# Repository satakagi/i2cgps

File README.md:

# I2CGPS

これは一般的なGPSレシーバ (GY-NEO6MV2など、UART 9600bpsでNMEA0183形式のデータを出力する。3.3Vでも動くもの) をI2Cインターフェースで使用できるようにするものです。メインコンピューターのUARTに余裕がないときに便利かもしれません。Arduino Pro Mini 3.3V (8MHz)でI2Cに変換しています。GY-NEO6MV2+Arduino Pro Mini 3.3V互換ボード+CHIRIMEN PiZero環境で動作確認をしました。

https://github.com/ckuethe/i2cgps をフォークして開発しました。そのため、i2cのインターフェース仕様はフォーク元に準じます。
ただ、私のArduino環境ではオリジナルのソース(.ino)はうまく動かなかったので、GPSライブラリの変更を伴う作り直しをしています。

原作者さんはATTiny85への移行を目指したようですが未達、この実装もArduino(ATMega248)用です。

また、以下を追加しています。
* [chirimen](https://www.chirimen.org)用のドライバとサンプル：[chirimen](./chirimen/)ディレクトリ
* 実体配線図：[hardware](./hardware)
* 未検証ですが・・KiCadのプリント基板設計図：[hardware/KiCad/](./hardware/KiCad/)

## 準備するもの
* GPSレシーバ([GY-NEO6MV2](https://electronicwork.shop/items/625c1ca99fe3d707d725cbe1)で確認しています)
* Arduiono Pro Mini 3.3V (8MHz) （もしくはその互換ボード）：この配線図通りで動かすには3.3V版が必要です ([互換ボードは数百円](https://electronicwork.shop/items/64e2182be37f74003b45e342)で購入できると思います)
* Arduiono Pro Miniにファームウェア(スケッチ)を書き込むための環境(ハードとしてはFTDI USBシリアル変換アダプター([数百円](https://electronicwork.shop/items/63412a95c15c5a192180482f)で買えると思います)が必要です)
* [Chirimen Pi Zero 環境](https://tutorial.chirimen.org/pizero/)

## 動かし方
* ファームウェアの書き込み：Arduino Pro Mini 3.3V(もしくはその互換ボード)にUSB-シリアル(専用のものが安価に流通しています)に、ArduinoIDEで[i2cgps.ino](./i2cgps.ino)を書き込みます
* 実体配線図のようにつなぎます
* GPSレシーバが測位できていなくても、空のデータが送信されてくるため、Arduino側のLEDは点滅するはずです（点滅していないときはどこかに問題がある）
* 測位できるとGPSレシーバ側のLEDも点滅します(GY-NEO6MV2の場合)
* chirimen piZero環境で[サンプルコード(ドライバ付き)](./chirimen/main.js)を実行すると、データが出力されます

## 実体配線図

## ライセンス
ライセンスは原作者さんが明示していないので・・・　[The TAPR Open Hardware License](https://tapr.org/the-tapr-open-hardware-license/)を提示しておきます。

---

## 以下は原作者 (ckuetheさん)の作成されたREADMEです。

From time to time you want to attach a GPS to a microcontroller and
you're already using all the serial ports. Luckily we have another bus:
I2C. You could call it a kind of a controller-area-network, given that
there are master and slave devices, each of which has a unique address.

Unfortunately there are very few commercial
[I2C GPS](https://www.sparkfun.com/products/14414) receivers and they
just do NMEA over I2C. There are
[other projects](http://www.technoblogy.com/show?1LJI) that do something similar, but with a higher part count. 

This particular implementation rather wastefully uses an ATmega, eg. an
Arduino Nano.

### TODO

* port this to attiny85, eg. digispark

### Other Links

* https://playground.arduino.cc/Code/USIi2c/
* https://github.com/rambo/TinyWire/tree/master/TinyWireS
* https://github.com/lucullusTheOnly/TinyWire
* https://github.com/adafruit/TinyWireM
* https://github.com/harbaum/I2C-Tiny-USB/tree/master/digispark
* https://digistump.com/board/index.php?topic=2831.0
* https://digistump.com/board/index.php?topic=1147.0
* https://digistump.com/wiki/digispark/tutorials/lcd

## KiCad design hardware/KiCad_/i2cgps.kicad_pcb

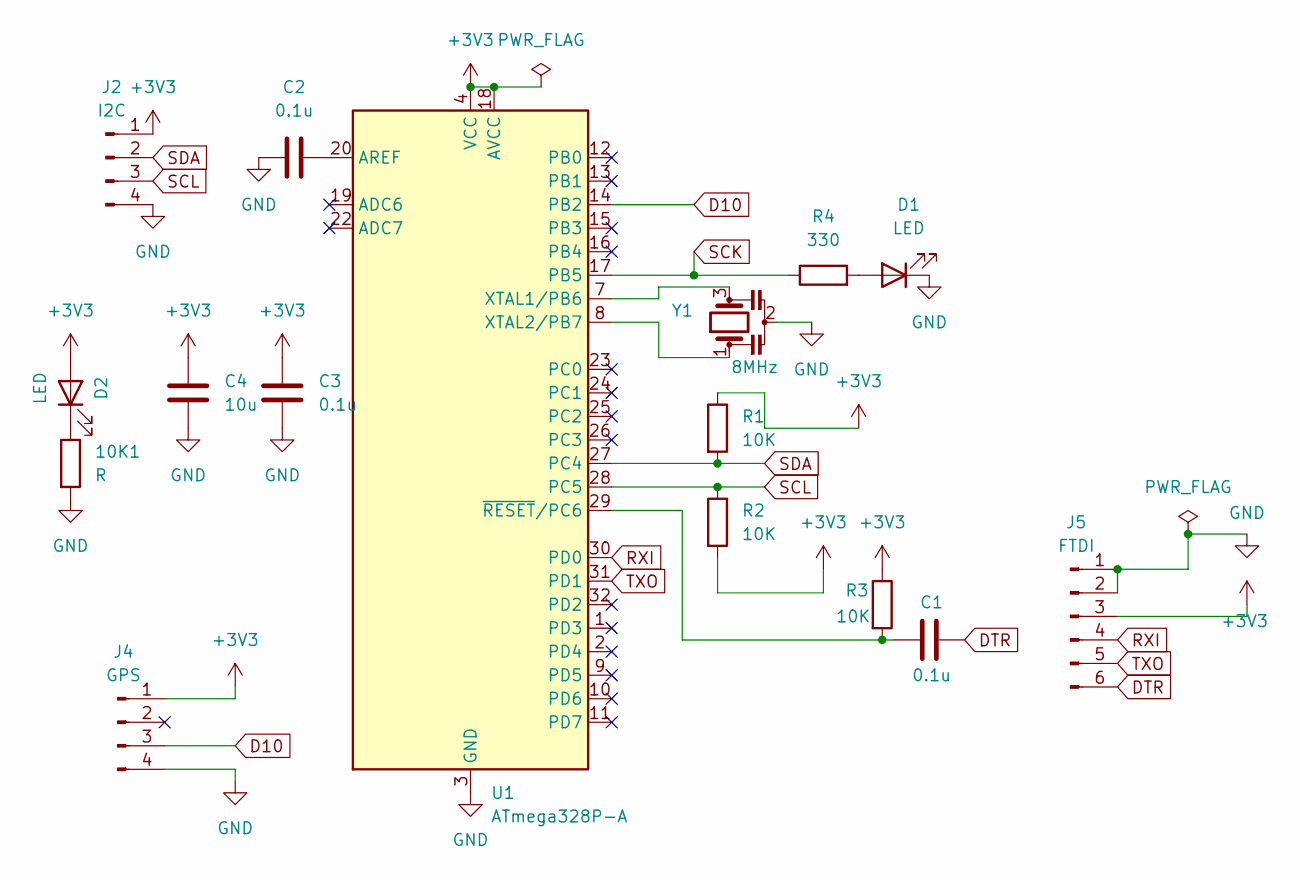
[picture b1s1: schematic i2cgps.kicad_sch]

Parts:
10K1: R; R_Axial_DIN0204_L3.6mm_D1.6mm_P5.08mm_Horizontal
C1, C2, C3: 0.1u; C_Disc_D3.0mm_W2.0mm_P2.50mm
C4: 10u; C_Disc_D3.0mm_W2.0mm_P2.50mm
D1, D2: LED; LED_D3.0mm
J2: I2C; PinHeader_1x04_P2.54mm_Vertical
J4: GPS; PinHeader_1x04_P2.54mm_Vertical
J5: FTDI; PinSocket_1x06_P2.00mm_Vertical
R1, R2, R3: 10K; R_Axial_DIN0204_L3.6mm_D1.6mm_P5.08mm_Horizontal
R4: 330; R_Axial_DIN0204_L3.6mm_D1.6mm_P5.08mm_Horizontal
U1: ATmega328P-A; TQFP-32_7x7mm_P0.8mm
Y1: 8MHz; Resonator_Murata_DSN6-3Pin_W7.0mm_H2.5mm

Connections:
+3V3: C3.1, C4.1, D2.2 (A), J2.1, J4.1, J5.3, R1.1, R2.2, R3.1, U1.4 (VCC), U1.6 (VCC), U1.18 (AVCC)
D10: J4.3, U1.14 (PB2)
DTR: C1.1, J5.6
GND: 10K1.2, C2.2, C3.2, C4.2, D1.1 (K), J2.4, J4.4, J5.1, J5.2, U1.3 (GND), U1.5 (GND), U1.21 (GND), Y1.2
unnamed: D1.2 (A), R4.2
unnamed: 10K1.1, D2.1 (K)
unnamed: C2.1, U1.20 (AREF)
unnamed: U1.7 (XTAL1/PB6), Y1.3
unnamed: U1.8 (XTAL2/PB7), Y1.1
unnamed: C1.2, R3.2, U1.29 (~RESET/PC6)
RXI: J5.4, U1.30 (PD0)
SCK: R4.1, U1.17 (PB5)
SCL: J2.3, R2.1, U1.28 (PC5)
SDA: J2.2, R1.2, U1.27 (PC4)
TXO: J5.5, U1.31 (PD1)

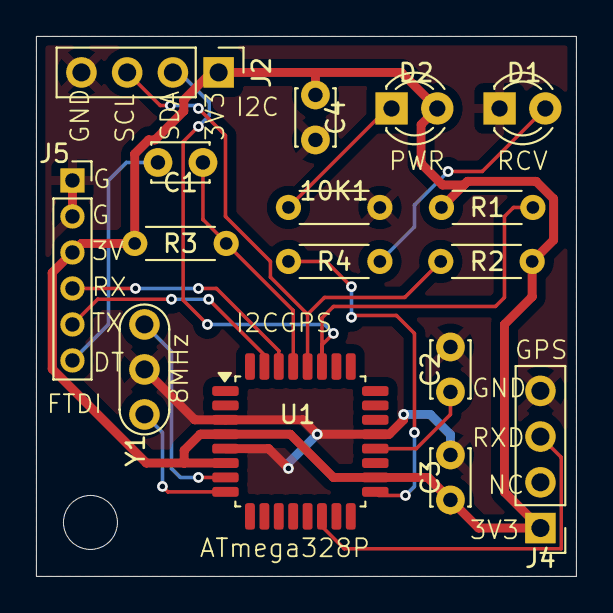
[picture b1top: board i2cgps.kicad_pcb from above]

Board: 2 copper layers, 30.0 x 30.0 mm, 16 parts (0 on the bottom side), 15 nets.

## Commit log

2025-08-14 Add schematics
2025-08-15 renamed: hardware/kiCad/imgs/PDBimg.png -> hardware/kiCad/imgs/PCBimg.png
